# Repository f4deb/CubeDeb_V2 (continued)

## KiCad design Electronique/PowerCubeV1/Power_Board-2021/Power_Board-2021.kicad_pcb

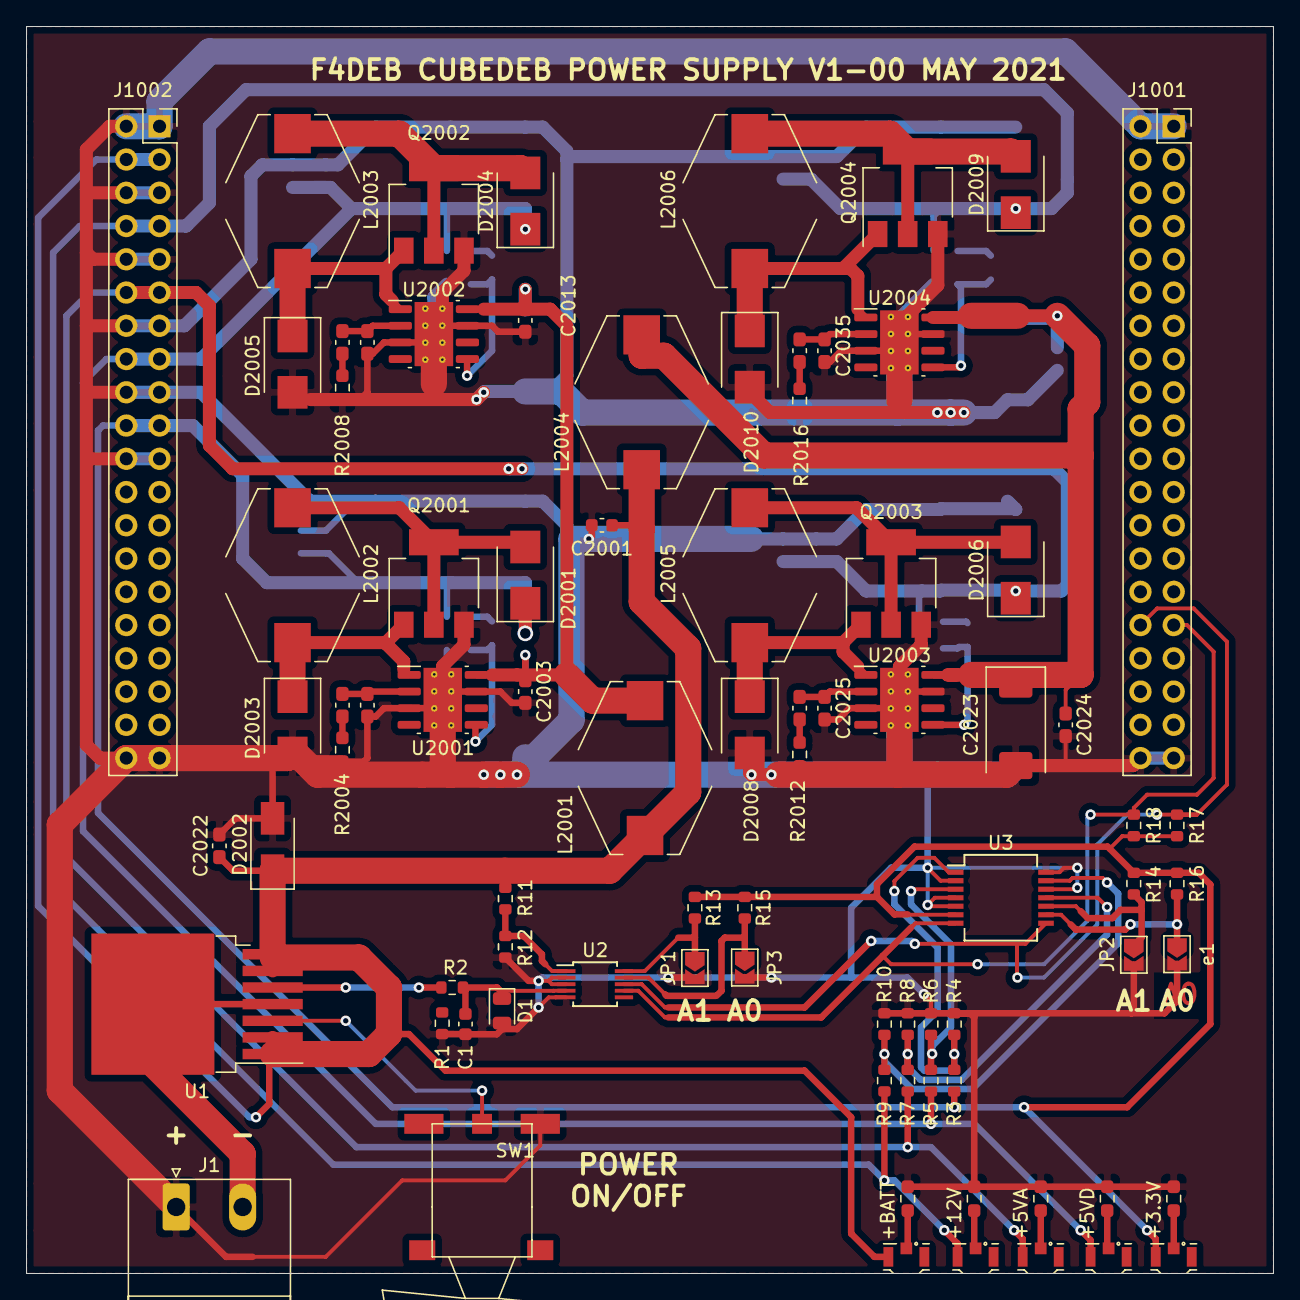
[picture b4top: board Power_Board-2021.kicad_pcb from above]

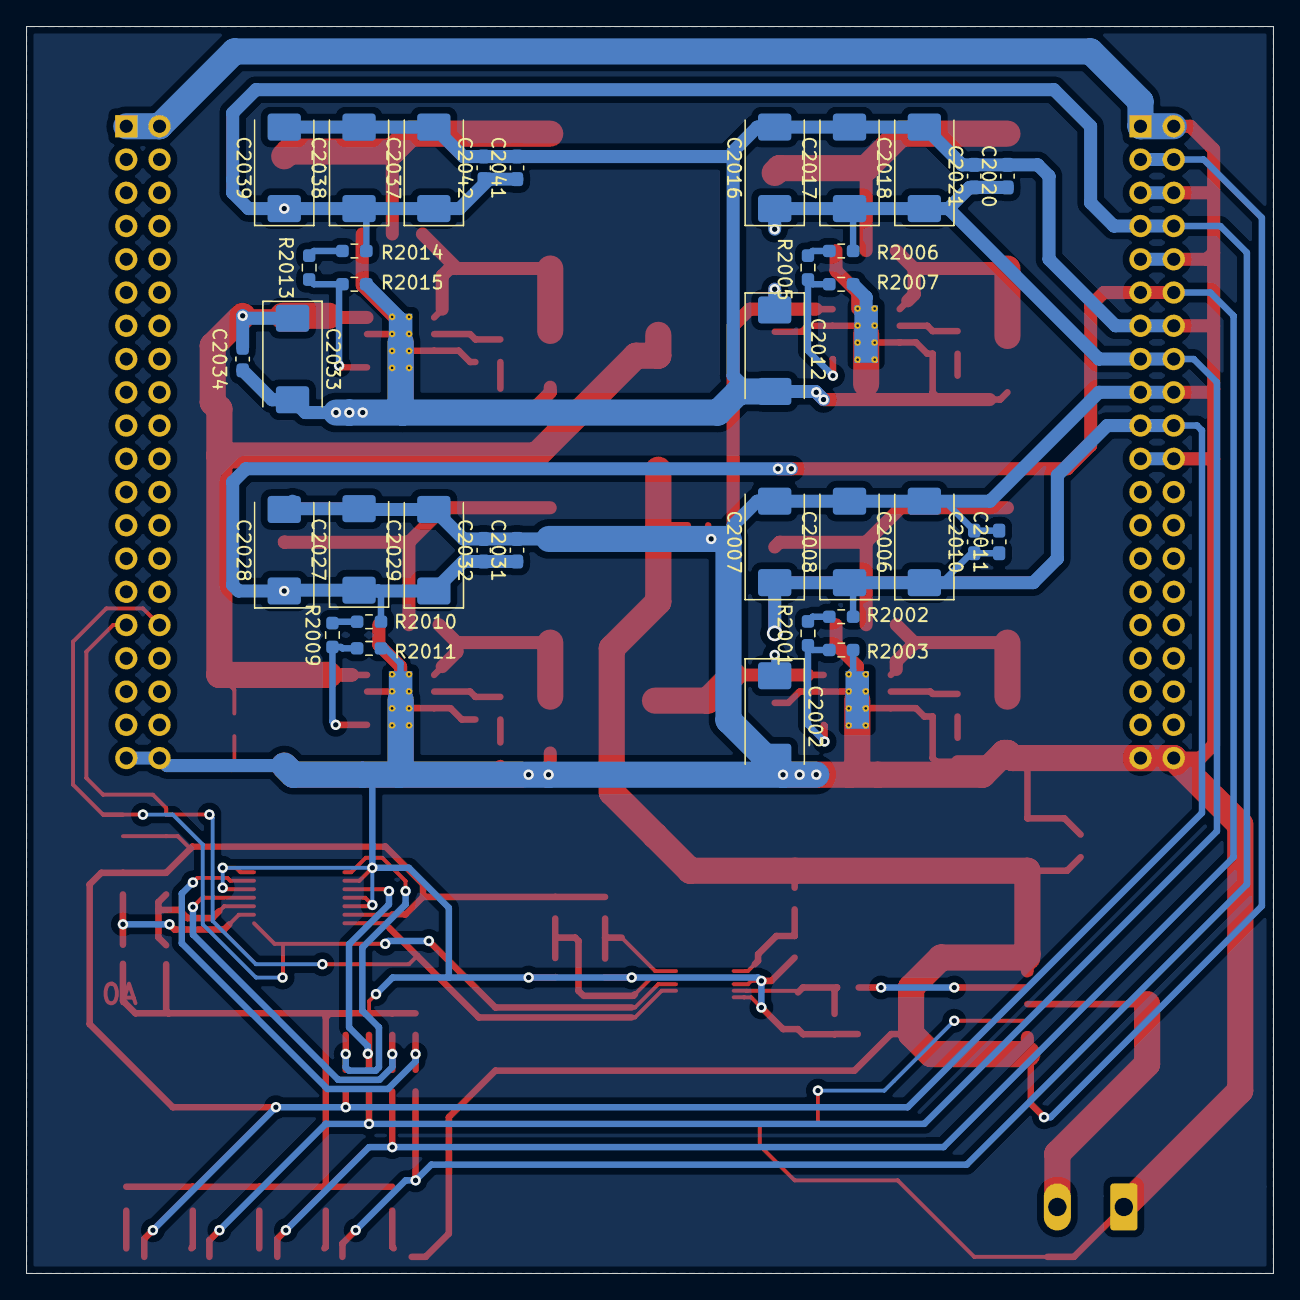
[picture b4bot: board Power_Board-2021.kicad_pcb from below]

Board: 2 copper layers, 95.2 x 95.2 mm, 118 parts (36 on the bottom side), 52 nets.

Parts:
C1: C; C_0603_1608Metric
C2001: 47n; C_0603_1608Metric
C2002, C2012: 10µ/35V; CP_EIA-7343-31_Kemet-D
C2003, C2013, C2022, C2024, C2034: 47n; C_0603_1608Metric_Pad1.08x0.95mm_HandSolder
C2004, C2014, C2025, C2035: 220p; C_0603_1608Metric_Pad1.08x0.95mm_HandSolder
C2005, C2015, C2026, C2036: 22n; C_0603_1608Metric_Pad1.08x0.95mm_HandSolder
C2006, C2016, C2027, C2037: CP; CP_EIA-7343-31_Kemet-D
C2007, C2008, C2017, C2018, C2028, C2029, C2038, C2039: 100µ; CP_EIA-7343-31_Kemet-D
C2010, C2011, C2020, C2021, C2031, C2032, C2041, C2042: 100n; C_0603_1608Metric_Pad1.08x0.95mm_HandSolder
C2023, C2033: 10µ/25V; CP_EIA-7343-31_Kemet-D
D1: D_Zener; D_0805_2012Metric
D2001, D2003, D2004, D2005, D2006, D2008, D2009, D2010: MBRS130LT3G; D_SMB
D2002: SMAJ36A; D_SMA
D2011, D2012, D2013, D2014, D2015: LED_Dual_CCA; LED_LiteOn_LTST-S326
J1: Conn_01x02_Male; PhoenixContact_MSTBA_2,5_2-G-5,08_1x02_P5.08mm_Horizontal
J1001, J1002: Conn_02x20_Odd_Even; PinSocket_2x20_P2.54mm_Vertical
JP1, JP2, JP3: SolderJumper_2_Open; SolderJumper-2_P1.3mm_Open_TrianglePad1.0x1.5mm
L2001, L2004: 10µH/4.7A; L_Bourns-SRR1005
L2002, L2003, L2005, L2006: 22µH/3.3A; L_Bourns-SRR1005
Q2001, Q2002, Q2003, Q2004: IRLL3303; SOT-223-3_TabPin2
R1, R2, R3, R4, R5, R6, R7, R8, R9, R10, R14, R16: R; R_0603_1608Metric
R11: 100k; R_0603_1608Metric
R12, R17, R18: 10k; R_0603_1608Metric
R13, R15: 47k; R_0603_1608Metric
R2001: 5k6; R_0603_1608Metric_Pad0.98x0.95mm_HandSolder
R2002: 0; R_0603_1608Metric_Pad0.98x0.95mm_HandSolder
R2003, R2007, R2011: 3k3; R_0603_1608Metric_Pad0.98x0.95mm_HandSolder
R2004, R2008, R2012, R2016: 4k7; R_0603_1608Metric_Pad0.98x0.95mm_HandSolder
R2005, R2009: 10k; R_0603_1608Metric_Pad0.98x0.95mm_HandSolder
R2006, R2010, R2019, R2020: 1k; R_0603_1608Metric_Pad0.98x0.95mm_HandSolder
R2013: 22k; R_0603_1608Metric_Pad0.98x0.95mm_HandSolder
R2014: 1.5k; R_0603_1608Metric_Pad0.98x0.95mm_HandSolder
R2015: 2k7; R_0603_1608Metric_Pad0.98x0.95mm_HandSolder
R2017, R2018: 3.3k; R_0603_1608Metric_Pad0.98x0.95mm_HandSolder
R2021: 470; R_0603_1608Metric_Pad0.98x0.95mm_HandSolder
SW1: SW_SPST; BOUTON_SWITCH_CMS
U1: BTS50055-1TMA; TO-263-7_TabPin4
U2: MCP3427-xUN; MSOP-10_3x3mm_P0.5mm
U3: MCP3428; SSOP-14_5.3x6.2mm_P0.65mm
U2001, U2002, U2003, U2004: L5973D; SOIC-8-1EP_3.9x4.9mm_P1.27mm_EP2.95x4.9mm_Mask2.71x3.4mm_Th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
e1: SolderJumper_2_Open; SolderJumper-2_P1.3mm_Open_TrianglePad1.0x1.5mm

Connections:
+3V3: C2006.1, C2007.1, C2008.1, C2010.1, C2011.1, D2001.1, D2015.3, J1002.19, J1002.20, R3.1, R13.1, R14.1, R15.1, R16.1, R17.1, R18.1, R2002.1, U3.6
+5VA: C2027.1, C2028.1, C2029.1, C2031.1, C2032.1, D2006.1, D2013.3, J1002.11, J1002.12, R7.1, R2010.1
+5VD: C2016.1, C2017.1, C2018.1, C2020.1, C2021.1, D2004.1, D2014.3, J1002.15, J1002.16, R5.1, R2006.1
+12V: C2037.1, C2038.1, C2039.1, C2041.1, C2042.1, D2009.1, D2012.3, J1002.7, J1002.8, R9.1, R2014.1
+BATT: C2001.1, C2022.1, D2002.1, D2011.3, J1002.3, J1002.4, L2001.1, L2004.1, R11.2, U1.1, U1.2, U1.6, U1.7
+VSW: J1.2, U1.4
/SCL0: J1001.32, R17.2, U2.8, U3.8
/SDA0: J1001.31, R18.2, U2.7, U3.7
GND: C1.1, C2001.2, C2002.2, C2003.2, C2004.2, C2006.2, C2007.2, C2008.2, C2010.2, C2011.2, C2012.2, C2013.2, C2014.2, C2016.2, C2017.2, C2018.2, C2020.2, C2021.2, C2022.2, C2023.2, C2024.2, C2025.2, C2027.2, C2028.2, C2029.2, C2031.2, C2032.2, C2033.2, C2034.2, C2035.2, C2037.2, C2038.2, C2039.2, C2041.2, C2042.2, D1.2, D2002.2, D2003.2, D2005.2, D2008.2, D2010.2, J1.1, J1001.1, J1001.2, J1001.39, J1001.40, J1002.1, J1002.2, J1002.5, J1002.6, J1002.9, J1002.10, J1002.13, J1002.14, J1002.17, J1002.18, J1002.21, J1002.22, J1002.39, J1002.40, JP1.2, JP2.2, JP3.2, Q2001.3, Q2002.3, Q2003.3, Q2004.3, R1.2, R4.2, R6.2, R8.2, R10.2, R12.2, R2003.2, R2004.2, R2007.2, R2008.2, R2011.2, R2012.2, R2015.2, R2016.2, R2017.2, R2018.2, R2019.2, R2020.2, R2021.2, SW1.1, U2.2, U2.3, U2.5, U3.2, U3.4, U3.5, U3.12, U3.14, U2001.3, U2001.7, U2001.9, U2002.3, U2002.7, U2002.9, U2003.3, U2003.7, U2003.9, U2004.3, U2004.7, U2004.9, e1.2
unnamed: C1.2, D1.1, R2.1, U2.4
unnamed: C2002.1, C2003.1, C2012.1, C2013.1, L2001.2, U2001.8, U2002.8
unnamed: C2004.1, C2005.1, U2001.2
unnamed: C2005.2, R2004.1
unnamed: C2014.1, C2015.1, U2002.2
unnamed: C2015.2, R2008.1
unnamed: C2023.1, C2024.1, C2033.1, C2034.1, L2004.2, U2003.8, U2004.8
unnamed: C2025.1, C2026.1, U2003.2
unnamed: C2026.2, R2012.1
unnamed: C2035.1, C2036.1, U2004.2
unnamed: C2036.2, R2016.1
unnamed: D2001.2, L2002.2, Q2001.2
unnamed: D2003.1, L2002.1, Q2001.1, U2001.1
unnamed: D2004.2, L2003.2, Q2002.2
unnamed: D2005.1, L2003.1, Q2002.1, U2002.1
unnamed: D2006.2, L2005.2, Q2003.2
unnamed: D2008.1, L2005.1, Q2003.1, U2003.1
unnamed: D2009.2, L2006.2, Q2004.2
unnamed: D2010.1, L2006.1, Q2004.1, U2004.1
unnamed: D2011.2, R2017.1
unnamed: D2012.2, R2018.1
unnamed: D2013.2, R2019.1
unnamed: D2014.2, R2020.1
unnamed: D2015.2, R2021.1
unnamed: JP1.1, R13.2, U2.10
unnamed: JP2.1, R14.2, U3.10
unnamed: JP3.1, R15.2, U2.9
unnamed: R1.1, R2.2, U1.5
unnamed: R3.2, R4.1, U3.1
unnamed: R5.2, R6.1, U3.3
unnamed: R7.2, R8.1, U3.11
unnamed: R9.2, R10.1, U3.13
unnamed: R11.1, R12.1, U2.1
unnamed: R16.2, U3.9, e1.1
unnamed: R2001.1, R2002.2
unnamed: R2001.2, R2003.1, U2001.5
unnamed: R2005.1, R2006.2
unnamed: R2005.2, R2007.1, U2002.5
unnamed: R2009.1, R2010.2
unnamed: R2009.2, R2011.1, U2003.5
unnamed: R2013.1, R2014.2
unnamed: R2013.2, R2015.1, U2004.5
unnamed: SW1.2, U1.3
